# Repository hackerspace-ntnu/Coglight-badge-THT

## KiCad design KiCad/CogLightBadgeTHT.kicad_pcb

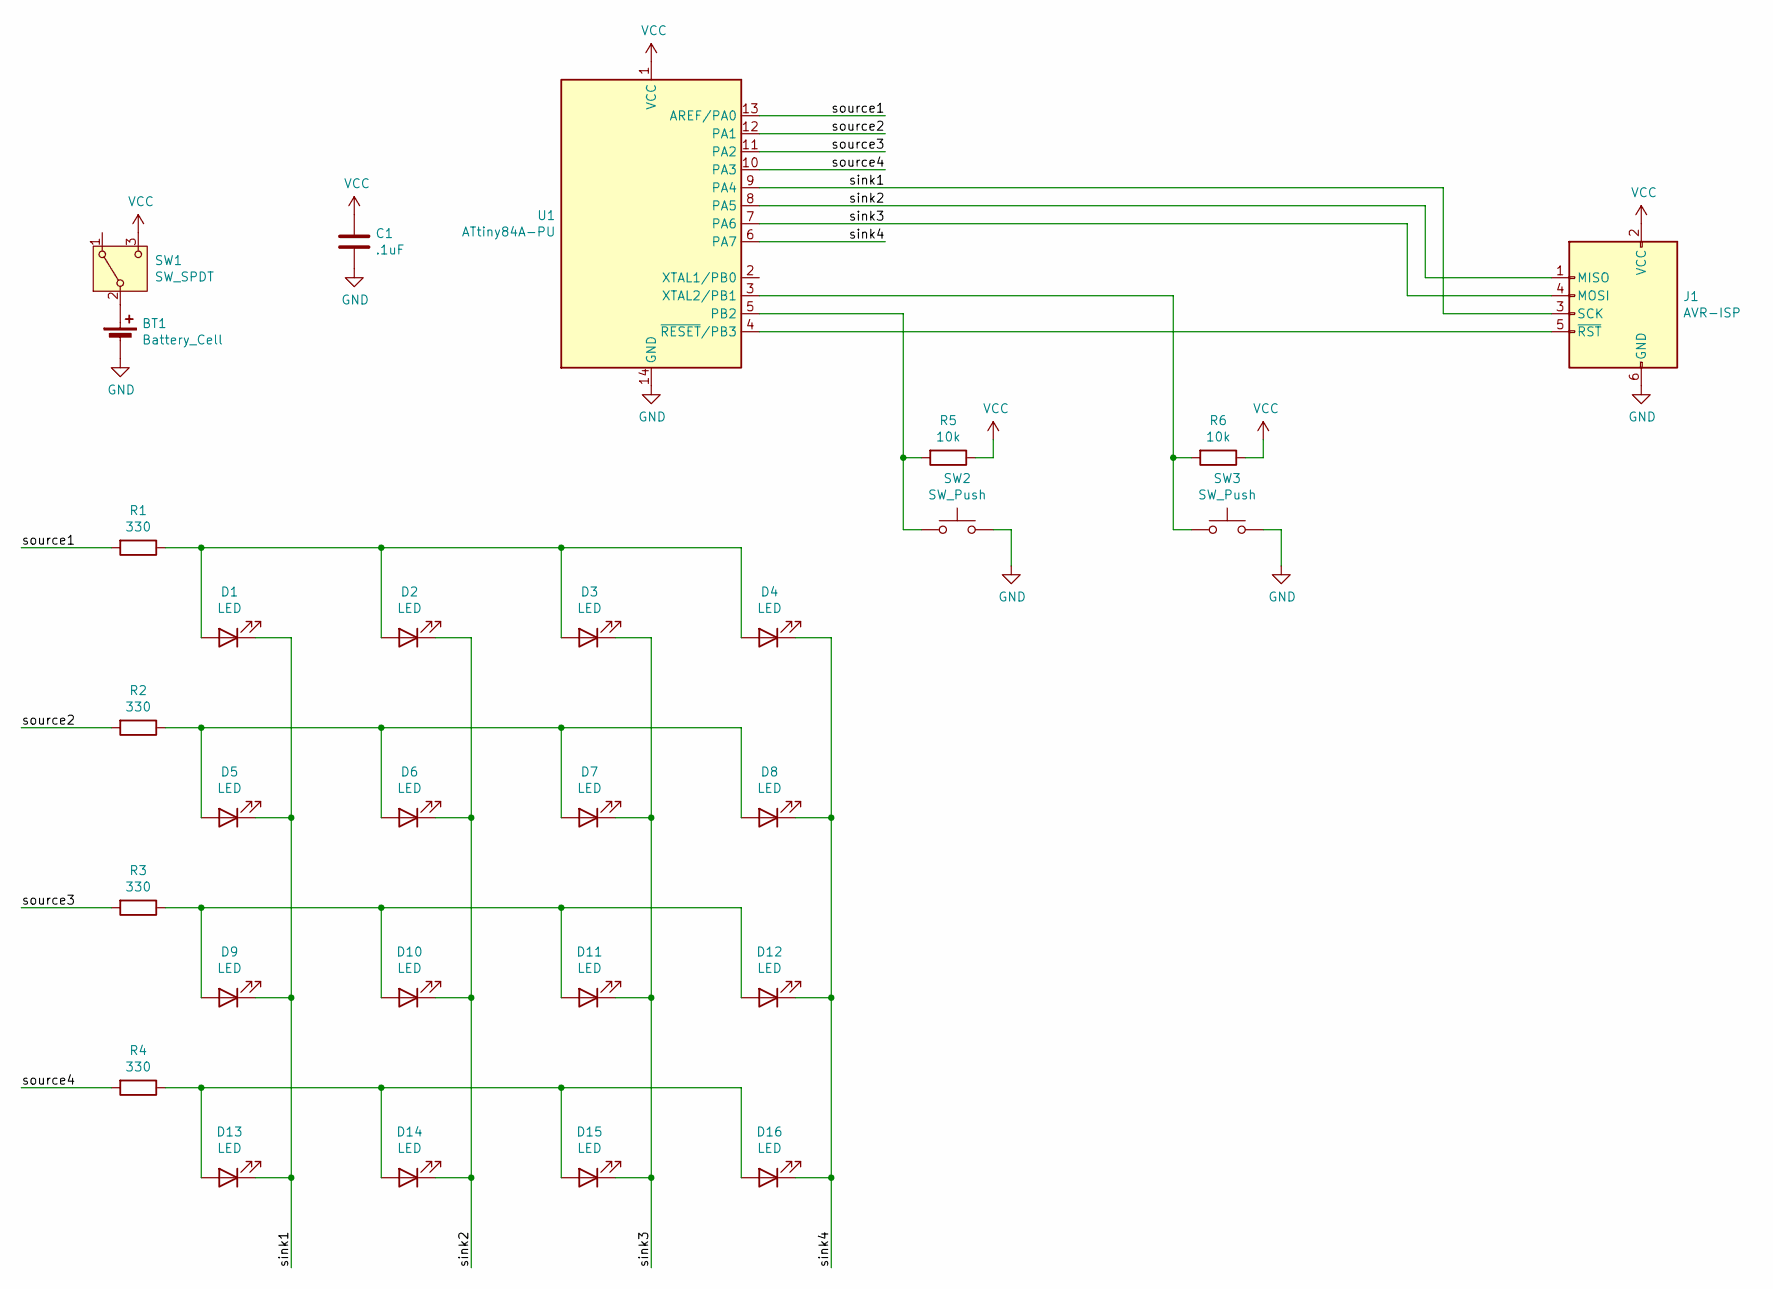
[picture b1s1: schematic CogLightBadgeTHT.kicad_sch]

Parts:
BT1: Battery_Cell; MP000362_CR2032_Holder_THT
C1: .1uF; C_Disc_D5.0mm_W2.5mm_P5.00mm
D1, D2, D3, D4, D5, D6, D7, D8, D9, D10, D11, D12, D13, D14, D15, D16: LED; LED_D5.0mm
J1: AVR-ISP; IDC-Header_2x03_P2.54mm_Vertical
R1, R2, R3, R4: 330; R_Axial_DIN0207_L6.3mm_D2.5mm_P7.62mm_Horizontal
R5, R6: 10k; R_Axial_DIN0207_L6.3mm_D2.5mm_P7.62mm_Horizontal
SW1: SW_SPDT; OS102011MA1QN1_SPDT_SlideSwithch_THT
SW2, SW3: SW_Push; SW_PUSH_6mm_H5mm
U1: ATtiny84A-PU; DIP-14_W7.62mm_LongPads

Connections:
/sink1: D1.1 (K), D5.1 (K), D9.1 (K), D13.1 (K), J1.3 (SCK), U1.9 (PA4)
/sink2: D2.1 (K), D6.1 (K), D10.1 (K), D14.1 (K), J1.1 (MISO), U1.8 (PA5)
/sink3: D3.1 (K), D7.1 (K), D11.1 (K), D15.1 (K), J1.4 (MOSI), U1.7 (PA6)
/sink4: D4.1 (K), D8.1 (K), D12.1 (K), D16.1 (K), U1.6 (PA7)
/source1: R1.2, U1.13 (AREF/PA0)
/source2: R2.2, U1.12 (PA1)
/source3: R3.2, U1.11 (PA2)
/source4: R4.2, U1.10 (PA3)
GND: BT1.2 (-), C1.2, J1.6 (GND), SW2.2, SW3.2, U1.14 (GND)
unnamed: BT1.1 (+), SW1.2 (B)
unnamed: D1.2 (A), D2.2 (A), D3.2 (A), D4.2 (A), R1.1
unnamed: D5.2 (A), D6.2 (A), D7.2 (A), D8.2 (A), R2.1
unnamed: D9.2 (A), D10.2 (A), D11.2 (A), D12.2 (A), R3.1
unnamed: D13.2 (A), D14.2 (A), D15.2 (A), D16.2 (A), R4.1
unnamed: J1.5 (~RST), U1.4 (~RESET/PB3)
unnamed: R5.2, SW2.1, U1.5 (PB2)
unnamed: R6.2, SW3.1, U1.3 (XTAL2/PB1)
VCC: C1.1, J1.2 (VCC), R5.1, R6.1, SW1.3 (C), U1.1 (VCC)

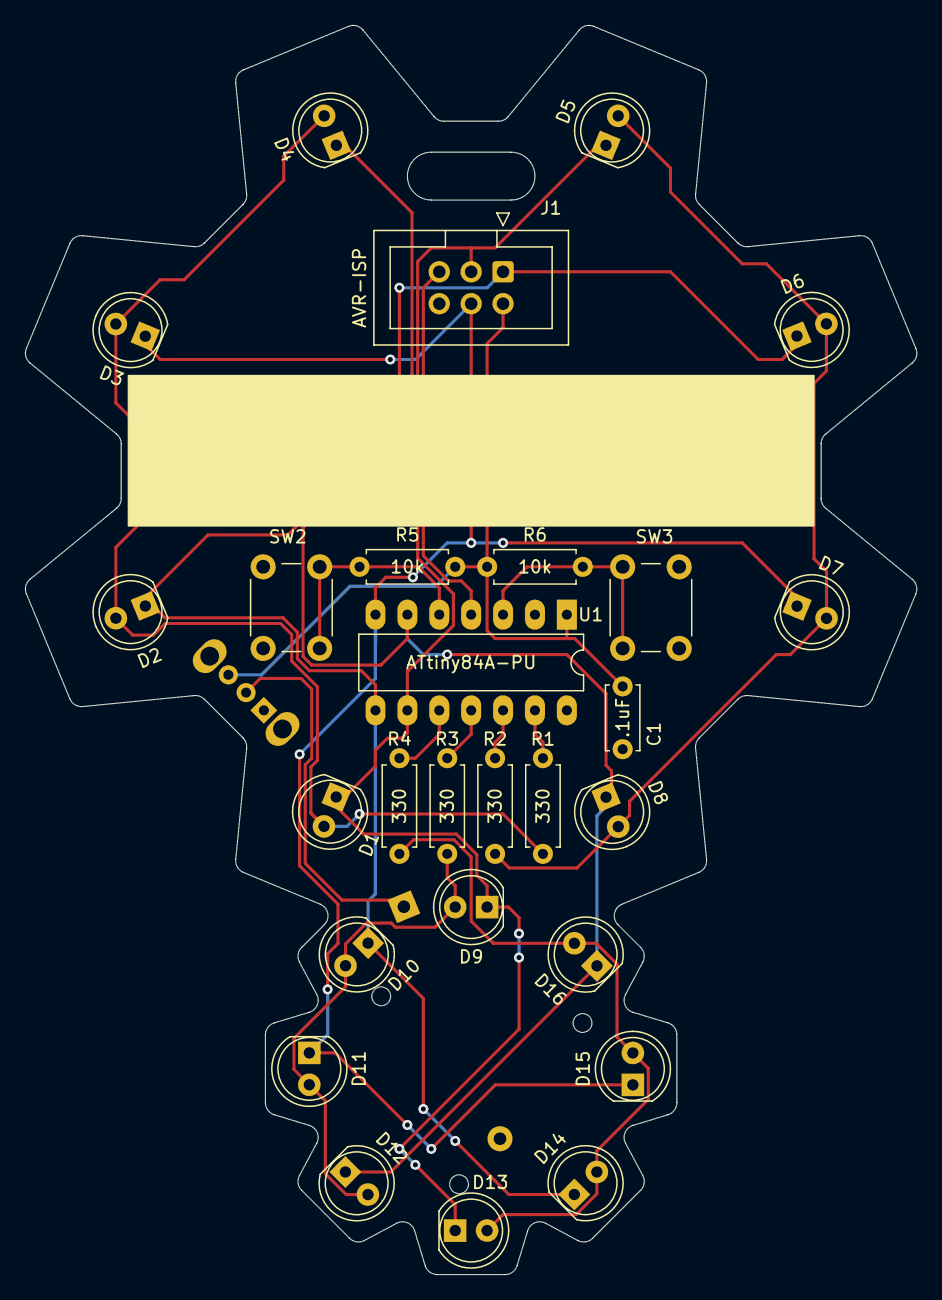
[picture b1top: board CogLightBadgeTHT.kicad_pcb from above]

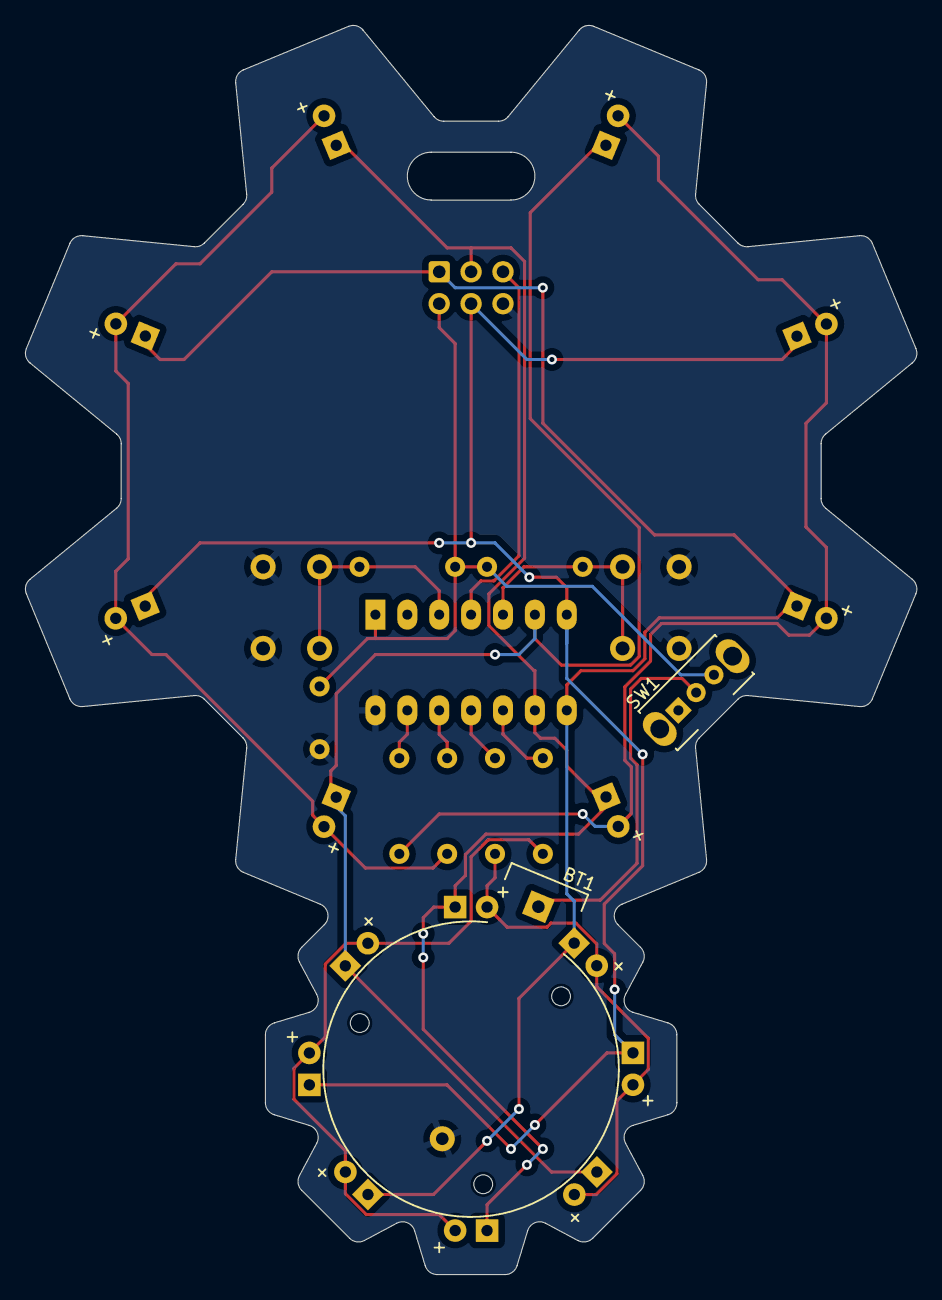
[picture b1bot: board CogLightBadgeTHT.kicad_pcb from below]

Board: 2 copper layers, 71.0 x 99.5 mm, 29 parts (2 on the bottom side), 18 nets.

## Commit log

2021-10-18 Only mark + for LED polarity
2022-03-19 Updated links documenting the gitignore file
2022-03-19 Reorganize project and add firmware
2025-02-27 Updated gerber files, wrote short documentation
2025-02-27 updated firmware with changes by Robin
2025-02-28 Moved arduino firmware to own folder, preserving atmel-speciffic code
